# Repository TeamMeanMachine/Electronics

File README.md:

# Team 2471 Custom PCBs

## NOTE:
Most of our PCBs require the Digikey PCB Library available at https://github.com/Digi-Key/digikey-kicad-library as well as the Sparkfun libraries available at https://github.com/sparkfun/SparkFun-KiCad-Libraries

They also frequently require the library files contained in the `Core` folder of this repository

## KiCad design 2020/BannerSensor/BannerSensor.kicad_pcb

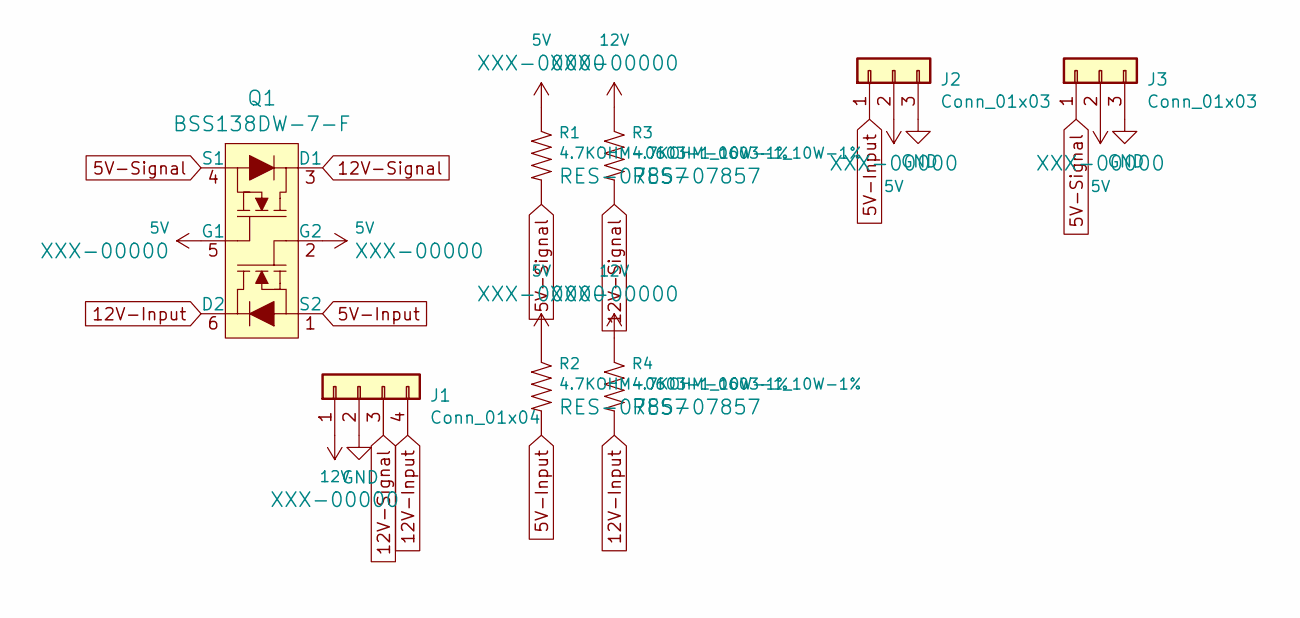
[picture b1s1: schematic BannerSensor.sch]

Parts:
J1: Conn_01x04; 1X04_NO_SILK
J2, J3: Conn_01x03; JST_XH_B3B-XH-A_1x03_P2.50mm_Vertical
Q1: BSS138DW-7-F; SOT-363; MPN BSS138DW-7-F; Digi-Key_PN BSS138DW-FDICT-ND
R1, R2, R3, R4: 4.7KOHM-0603-1_10W-1%; R_0603_1608Metric

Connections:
5V: J2.2, J3.2, Q1.2 (G2), Q1.5 (G1), R1.1, R2.1
5V-Input: J2.1, Q1.1 (S2), R2.2
5V-Signal: J3.1, Q1.4 (S1), R1.2
12V: J1.1, R3.1, R4.1
12V-Input: J1.4, Q1.6 (D2), R4.2
12V-Signal: J1.3, Q1.3 (D1), R3.2
GND: J1.2, J2.3, J3.3

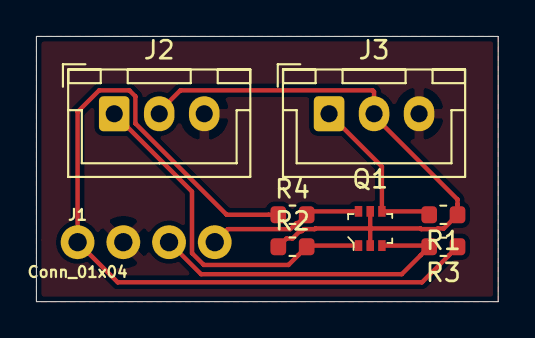
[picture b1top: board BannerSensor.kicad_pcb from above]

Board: 2 copper layers, 25.7 x 14.7 mm, 8 parts (0 on the bottom side), 7 nets.

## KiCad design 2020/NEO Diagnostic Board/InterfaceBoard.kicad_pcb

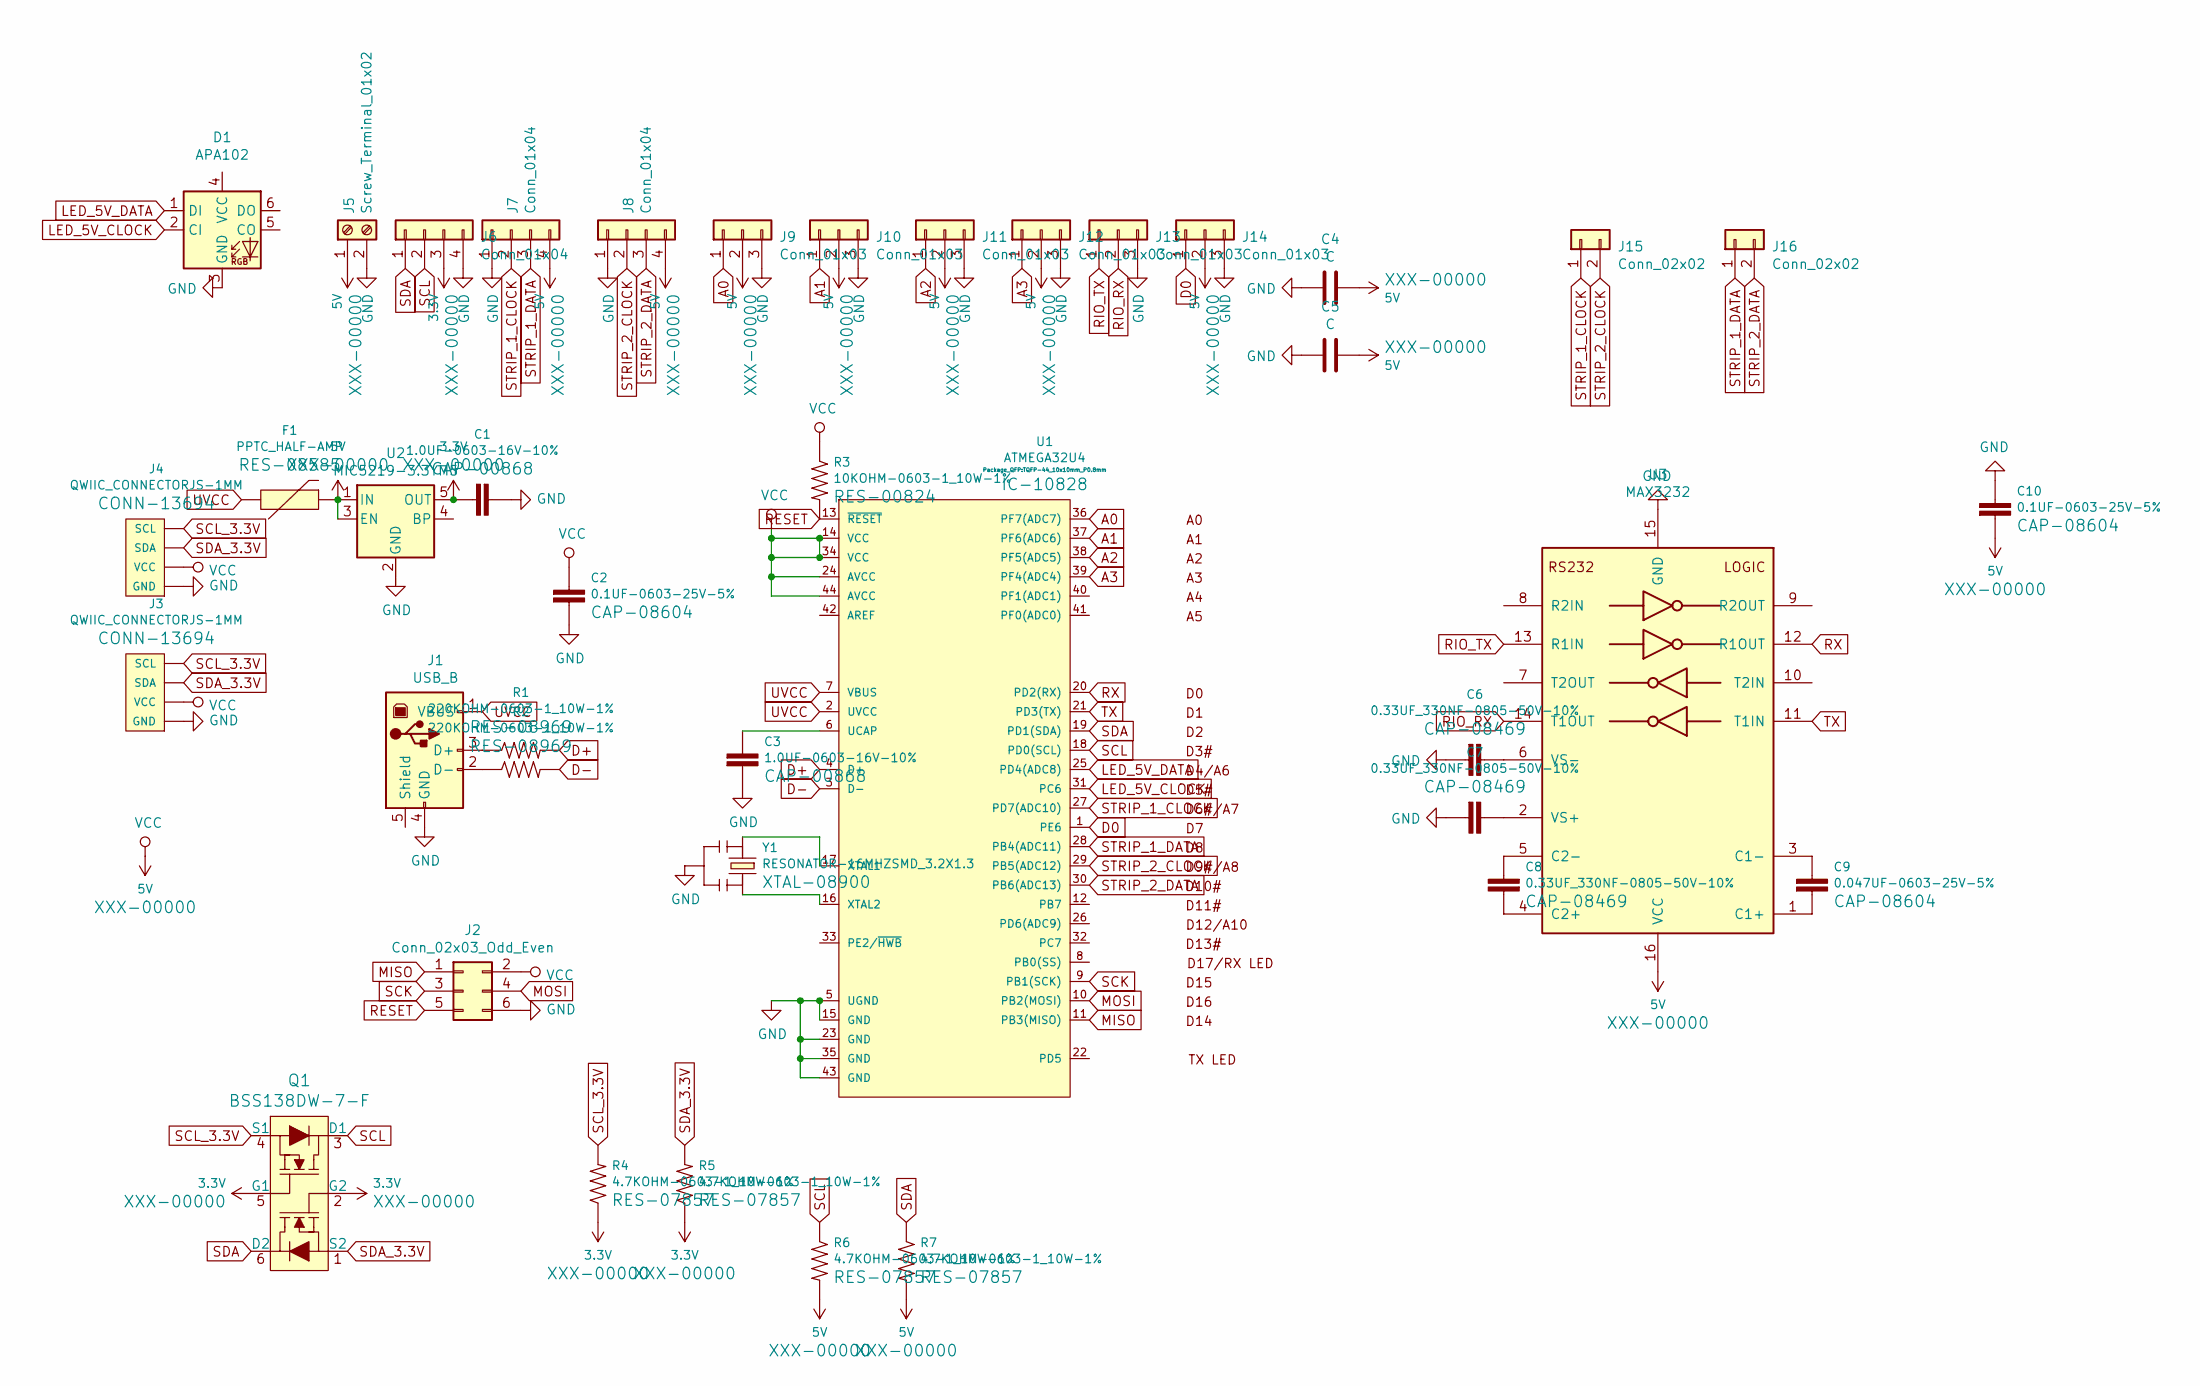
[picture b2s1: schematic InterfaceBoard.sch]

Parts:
C1, C3: 1.0UF-0603-16V-10%; C_0603_1608Metric
C2, C10: 0.1UF-0603-25V-5%; C_0603_1608Metric
C4, C5: C; CP_Radial_Tantal_D10.5mm_P5.00mm
C6, C7, C8: 0.33UF_330NF-0805-50V-10%; C_0603_1608Metric
C9: 0.047UF-0603-25V-5%; C_0603_1608Metric
D1: APA102; LED_RGB_PLCC-6
F1: PPTC_HALF-AMP; Fuse_1206_3216Metric
J1: USB_B; USB_B_OST_USB-B1HSxx_Horizontal
J2: Conn_02x03_Odd_Even; 2X3-NS
J3, J4: QWIIC_CONNECTORJS-1MM; 1X04_1MM_RA
J5: Screw_Terminal_01x02; SCREWTERMINAL-3.5MM-2-NS
J6, J7, J8: Conn_01x04; JST_XH_B4B-XH-A_1x04_P2.50mm_Vertical
J9, J10, J11, J12, J13, J14: Conn_01x03; JST_XH_B3B-XH-A_1x03_P2.50mm_Vertical
J15, J16: Conn_02x02; 1X02_NO_SILK
Q1: BSS138DW-7-F; SOT-363; MPN BSS138DW-7-F; Digi-Key_PN BSS138DW-FDICT-ND
R1, R2: 220KOHM-0603-1_10W-1%; R_0603_1608Metric
R3: 10KOHM-0603-1_10W-1%; R_0603_1608Metric
R4, R5, R6, R7: 4.7KOHM-0603-1_10W-1%; R_0603_1608Metric
U1: ATMEGA32U4; TQFP-44_10x10mm_P0.8mm
U2: MIC5219-3.3YM5; SOT-23-5
U3: MAX3232; TSSOP-16_4.4x5mm_P0.65mm
Y1: RESONATOR-16MHZSMD_3.2X1.3; RESONATOR-SMD-3.2X1.3_UNRESTRICTED

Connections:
3.3V: C1.2, J6.3, Q1.2 (G2), Q1.5 (G1), R4.1, R5.1, U2.5 (OUT)
5V: C2.1, C4.2, C5.2, C10.2, F1.2, J2.2, J3.2 (VCC), J4.2 (VCC), J5.1, J7.4, J8.4, J9.2, J10.2, J11.2, J12.2, J14.2, R3.1, R6.2, R7.2, U1.14 (VCC), U1.24 (AVCC), U1.34 (VCC), U1.44 (AVCC), U2.1 (IN), U2.3 (EN), U3.16 (VCC)
A0: J9.1, U1.36 (PF7(ADC7))
A1: J10.1, U1.37 (PF6(ADC6))
A2: J11.1, U1.38 (PF5(ADC5))
A3: J12.1, U1.39 (PF4(ADC4))
D0: J14.1, U1.1 (PE6)
D+: R1.2, U1.4 (D+)
D-: R2.2, U1.3 (D-)
GND: C1.1, C2.2, C3.2, C4.1, C5.1, C6.2, C7.2, C10.1, D1.3 (GND), J1.4 (GND), J2.6, J3.1 (GND), J4.1 (GND), J5.2, J6.4, J7.1, J8.1, J9.3, J10.3, J11.3, J12.3, J13.3, J14.3, U1.5 (UGND), U1.15 (GND), U1.23 (GND), U1.35 (GND), U1.43 (GND), U2.2 (GND), U3.15 (GND), Y1.2
LED_5V_CLOCK: D1.2 (CI), U1.31 (PC6)
LED_5V_DATA: D1.1 (DI), U1.25 (PD4(ADC8))
MISO: J2.1, U1.11 (PB3(MISO))
MOSI: J2.4, U1.10 (PB2(MOSI))
unnamed: C3.1, U1.6 (UCAP)
unnamed: C6.1, U3.6 (VS-)
unnamed: C7.1, U3.2 (VS+)
unnamed: C8.1, U3.4 (C2+)
unnamed: C8.2, U3.5 (C2-)
unnamed: C9.1, U3.3 (C1-)
unnamed: C9.2, U3.1 (C1+)
unnamed: J1.2 (D-), R2.1
unnamed: J1.3 (D+), R1.1
unnamed: U1.16 (XTAL2), Y1.3
unnamed: U1.17 (XTAL1), Y1.1
RESET: J2.5, R3.2, U1.13 (~RESET)
RIO_RX: J13.2, U3.14 (T1OUT)
RIO_TX: J13.1, U3.13 (R1IN)
RX: U1.20 (PD2(RX)), U3.12 (R1OUT)
SCK: J2.3, U1.9 (PB1(SCK))
SCL: J6.2, Q1.3 (D1), R6.1, U1.18 (PD0(SCL))
SCL_3.3V: J3.4 (SCL), J4.4 (SCL), Q1.4 (S1), R4.2
SDA: J6.1, Q1.6 (D2), R7.1, U1.19 (PD1(SDA))
SDA_3.3V: J3.3 (SDA), J4.3 (SDA), Q1.1 (S2), R5.2
STRIP_1_CLOCK: J7.2, J15.1, U1.27 (PD7(ADC10))
STRIP_1_DATA: J7.3, J16.1, U1.28 (PB4(ADC11))
STRIP_2_CLOCK: J8.2, J15.2, U1.29 (PB5(ADC12))
STRIP_2_DATA: J8.3, J16.2, U1.30 (PB6(ADC13))
TX: U1.21 (PD3(TX)), U3.11 (T1IN)
UVCC: F1.1, J1.1 (VBUS), U1.2 (UVCC), U1.7 (VBUS)

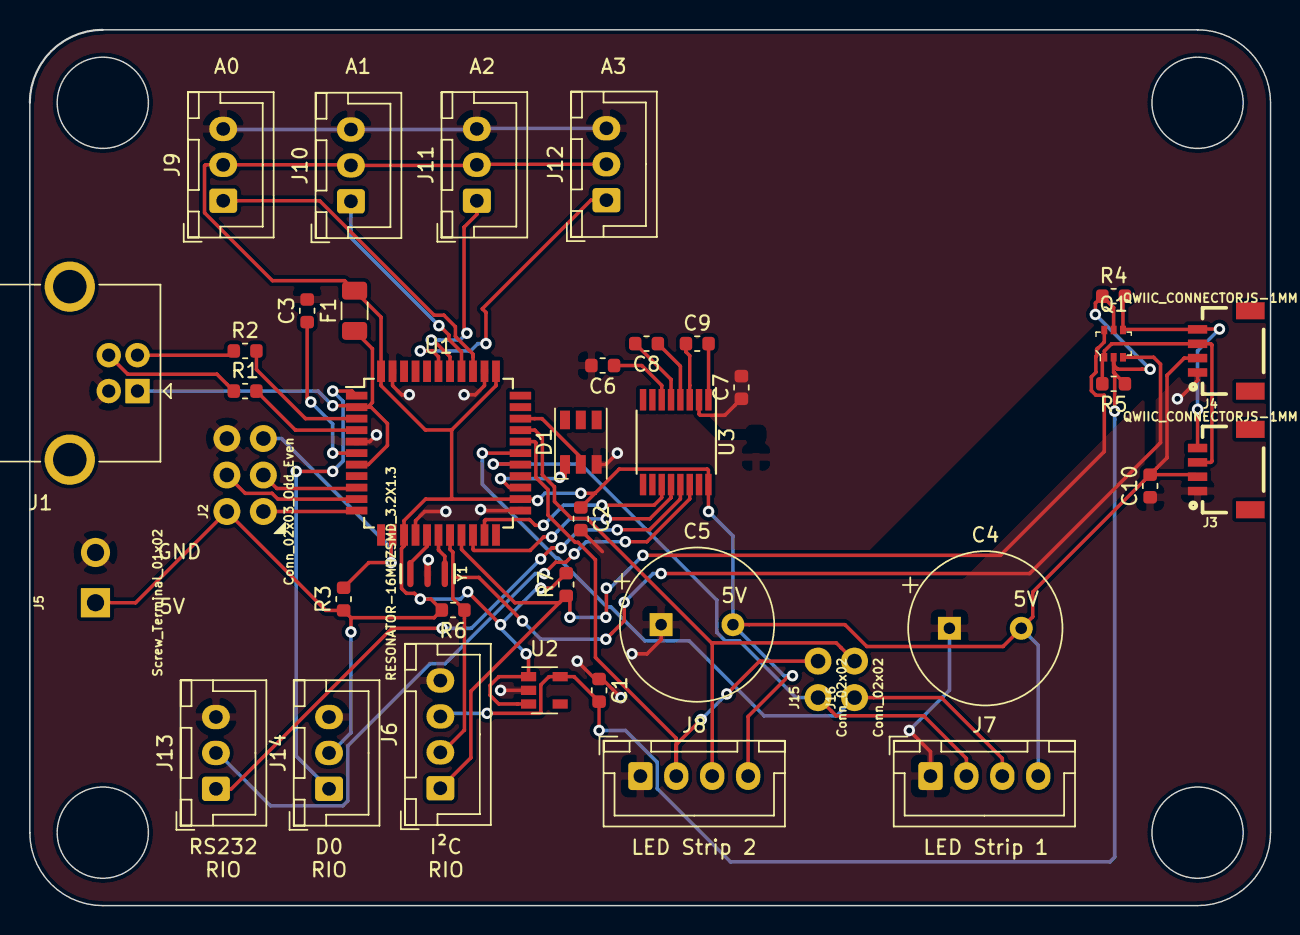
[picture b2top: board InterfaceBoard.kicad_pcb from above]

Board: 2 copper layers, 86.4 x 61.0 mm, 40 parts (0 on the bottom side), 40 nets.

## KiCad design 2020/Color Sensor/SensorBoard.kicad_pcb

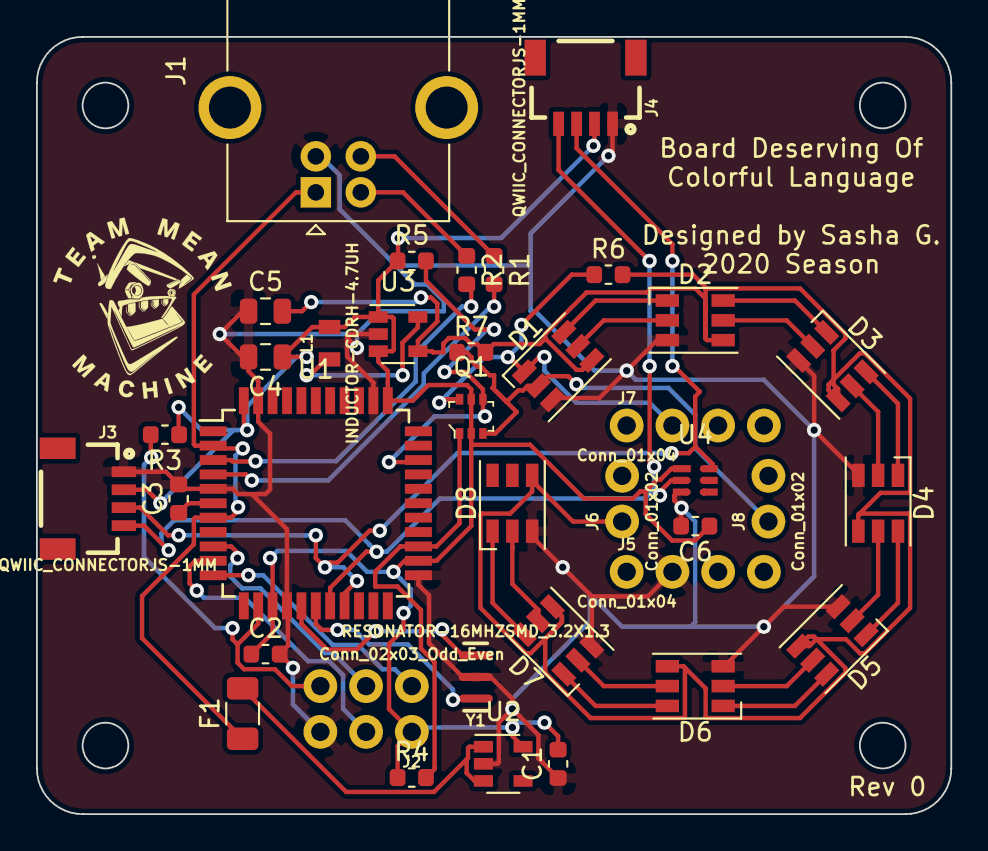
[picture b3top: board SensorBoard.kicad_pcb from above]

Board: 2 copper layers, 50.8 x 43.2 mm, 37 parts (0 on the bottom side), 37 nets.

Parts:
C1, C3: 1.0UF-0603-16V-10%; C_0603_1608Metric
C2, C6: 0.1UF-0603-25V-5%; C_0603_1608Metric
C4, C5: 10UF-0805-10V-10%; C_0805_2012Metric
D1, D2, D3, D4, D5, D6, D7, D8: APA102; LED_RGB_PLCC-6
F1: PPTC_HALF-AMP; Fuse_1206_3216Metric
J1: USB_B; USB_B_OST_USB-B1HSxx_Horizontal
J2: Conn_02x03_Odd_Even; 2X3-NS
J3, J4: QWIIC_CONNECTORJS-1MM; 1X04_1MM_RA
J5, J7: Conn_01x04; 1X04_ACTUAL_SIZE
J6, J8: Conn_01x02; 1X02_ACTUAL_SIZE
L1: INDUCTOR-CDRH-4.7UH; 0805
Q1: BSS138DW-7-F; SOT-363
R1, R2: 220KOHM-0603-1_10W-1%; R_0603_1608Metric
R3: 10KOHM-0603-1_10W-1%; R_0603_1608Metric
R4, R5, R6, R7: 4.7KOHM-0603-1_10W-1%; R_0603_1608Metric
U1: ATMEGA32U4; TQFP-44_10x10mm_P0.8mm
U2: MIC5219-3.3YM5; SOT-23-5
U3: XC9142; SOT-23-5
U4: TCS34725
Y1: RESONATOR-16MHZSMD_3.2X1.3; RESONATOR-SMD-3.2X1.3_UNRESTRICTED

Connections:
3.3V: C1.2, C2.1, C4.1, C6.1, J2.2, J3.2, J4.2, L1.2, Q1.2, Q1.5, R3.1, R4.1, R5.1, U1.14, U1.24, U1.34, U1.44, U2.5, U3.1, U3.3, U4.1
5V: C5.2, D1.4, D2.4, D3.4, D4.4, D5.4, D6.4, D7.4, D8.4, J6.1, R6.2, R7.2, U3.4
D+: R1.2, U1.4
D-: R2.2, U1.3
GND: C1.1, C2.2, C3.2, C4.2, C5.1, C6.2, D1.3, D2.3, D3.3, D4.3, D5.3, D6.3, D7.3, D8.3, J1.4, J2.6, J3.1, J4.1, J5.2, U1.5, U1.15, U1.23, U1.35, U1.43, U2.2, U3.2, U4.3, Y1.2
LED_3.3V_CLOCK: Q1.4, R5.2, U1.31
LED_3.3V_DATA: Q1.1, R4.2, U1.25
LED_5V_CLOCK: D1.2, J8.1, Q1.3, R7.1
LED_5V_DATA: D1.1, J7.2, Q1.6, R6.1
MISO: J2.1, U1.11
MOSI: J2.4, U1.10
unnamed: C3.1, U1.6
unnamed: D1.5, D2.2
unnamed: D1.6, D2.1
unnamed: D2.5, D3.2
unnamed: D2.6, D3.1
unnamed: D3.5, D4.2
unnamed: D3.6, D4.1
unnamed: D4.5, D5.2
unnamed: D4.6, D5.1
unnamed: D5.5, D6.2
unnamed: D5.6, D6.1
unnamed: D6.5, D7.2
unnamed: D6.6, D7.1
unnamed: D7.5, D8.2
unnamed: D7.6, D8.1
unnamed: F1.2, U2.1, U2.3
unnamed: J1.2, R2.1
unnamed: J1.3, R1.1
unnamed: L1.1, U3.5
unnamed: U1.16, Y1.3
unnamed: U1.17, Y1.1
RESET: J2.5, R3.2, U1.13
SCK: J2.3, U1.9
SCL: J3.4, J4.4, U1.18, U4.2
SDA: J3.3, J4.3, U1.19, U4.6
UVCC: F1.1, J1.1, U1.2, U1.7

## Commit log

2022-01-04 License file to sync things to github
2022-01-04 Added Circuit Boards
    + README
    + Most circuit boards
2022-01-08 Remove unneeded library
